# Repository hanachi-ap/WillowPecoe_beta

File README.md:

# WillowPecoe_beta

全国のWillowファンの皆様こんにちは。そしてβテストへようこそ。

## ビルドガイド(玄人向け)

MCUにProMicroを採用し、CherryMXスイッチ、PCB 3層サンドイッチと、ごくオーソドックスなスタイルを
採用しているので難しいところはないと思います。

基板がリバーシブルになっているので、パーツの取付面だけ注意ください。

## パーツリスト

- Pro Micro x1
- タクトスイッチ(2本足) x1
- MX用スイッチソケット x49
- ダイオード (TH or SMD) x50 
- フルカラーシリアルLED WS2812B x15 (opt)
- ロータリーエンコーダ x1  (opt)
  プッシュスイッチ対応。

  遊舎工房で販売している アメリカBourns社製 PEC12R-4222F-S0024 で動作を確認しています。
  その他秋月電子で販売しているロータリーエンコーダ（商品番号P-06357)もプシュスイッチ機能はありませんが動作確認済みです。

- 六角スペーサー(M2 7mm)  x13
- 六角スペーサー(M2 3.5mm) x6
- ネジ (M2 3mm) x38
- 2Uスタビライザ x1
- Cherry MX互換スイッチ x49
- キーキャップ (お好み)
  
## パーツの取付け
### 基板の表裏を決定
まず ロータリーエンコーダの位置を右か左か決めます。
 - 左側に置く場合、PCBのSide Aが表面になります。
 - 右側に置く場合、PCBのSide Bが表面になります。

### パーツのはんだ付け

#### ダイオード
- ダイオードは すべて裏面に取り付けます。 
  - SMD、TH どちらでも使えます。
  - 実際のところダイオードは表面につけても有効です。(見栄えの問題)
### スイッチソケット
- スイッチソケットはすべて裏面に取り付けます。

### RGB LED
- 表面側のパッドをジャンプさせます (Jump front sideと書いてあるところ)

- 表面に 3個、 裏面に12個取り付けます。
  - Side Aが表面の場合、 シルクのLED1からLED13に取り付けます。
  - Side Bが表面の場合、 シルクのLED16からLED30に取り付けます。

### ロータリーエンコーダ
- 表面からさして裏面をはんだ付けします。

### Pro Micro
 - ProMicroはコンスルーを使って表面に取り付けます。
 - ProMicroの実装面が内向きになるようにしてください。

### タクトスイッチ
  - 表面に取り付けます

## 組み立て

- トッププレートとPCBを3.5mmスペーサを使って取り付けます。
- スイッチを差し込みます。
- PCBと化粧板を7mmスペーサを使って取り付けます。
- トッププレートとボトムプレートを7mmスペーサを使って取り付けます。

## ファームウェア

- コンパイルしてください。ロリコンの位置によってキーマップが異なります。
  - Side A用: default
  - Side B用: side_b
  
## 既知の問題点

- アンダーグローの光がうまく廻りません。
  - アクリルプレートオプションを考慮します
  - 次の版では、簡単に表面の3つだけ優先的に光らせられるよう配線を見直します。
  - とりあえず表側の3個だけを光らすには 最初の5個だけを取り付けるか、ジャンパを這わせればOK。  

- PCBの表面に細かい油染みのような塗装ムラ?があります。
  - 製造委託先の品質に依存する問題かと思います。実質影響はありません。
  - 次の発注は別なところを考えてみます(量産のときはJLCPCBの価格は魅力なんだけど)
  
- ネジとスイッチが干渉する恐れがあるかも?
  - 作者手元のスイッチでは爪一枚入るくらいの余裕がありますが次の基板ではもう少し余裕持たせるようにします

- ファームウェアは開発途中です

- トッププレートのLEDを透過するスリットにはアクリルを埋め込む計画がありますが未実装です。
 
- 細かいキーレイアウトが作者の理想から少しだけ外れています。
  全体ををもう少し折り曲げたほうが好みなので修正が入るかもしれません

## 権利等
まだLICENSEを明記してませんが下記で公開する予定です。

- ファームウェア: GPL V2
- KiCAD設計データ: GPL V2
- KiCADフットプリント: MIT (thx foostan)
- 配列意匠: CC BY-SA 4.0 

以上です

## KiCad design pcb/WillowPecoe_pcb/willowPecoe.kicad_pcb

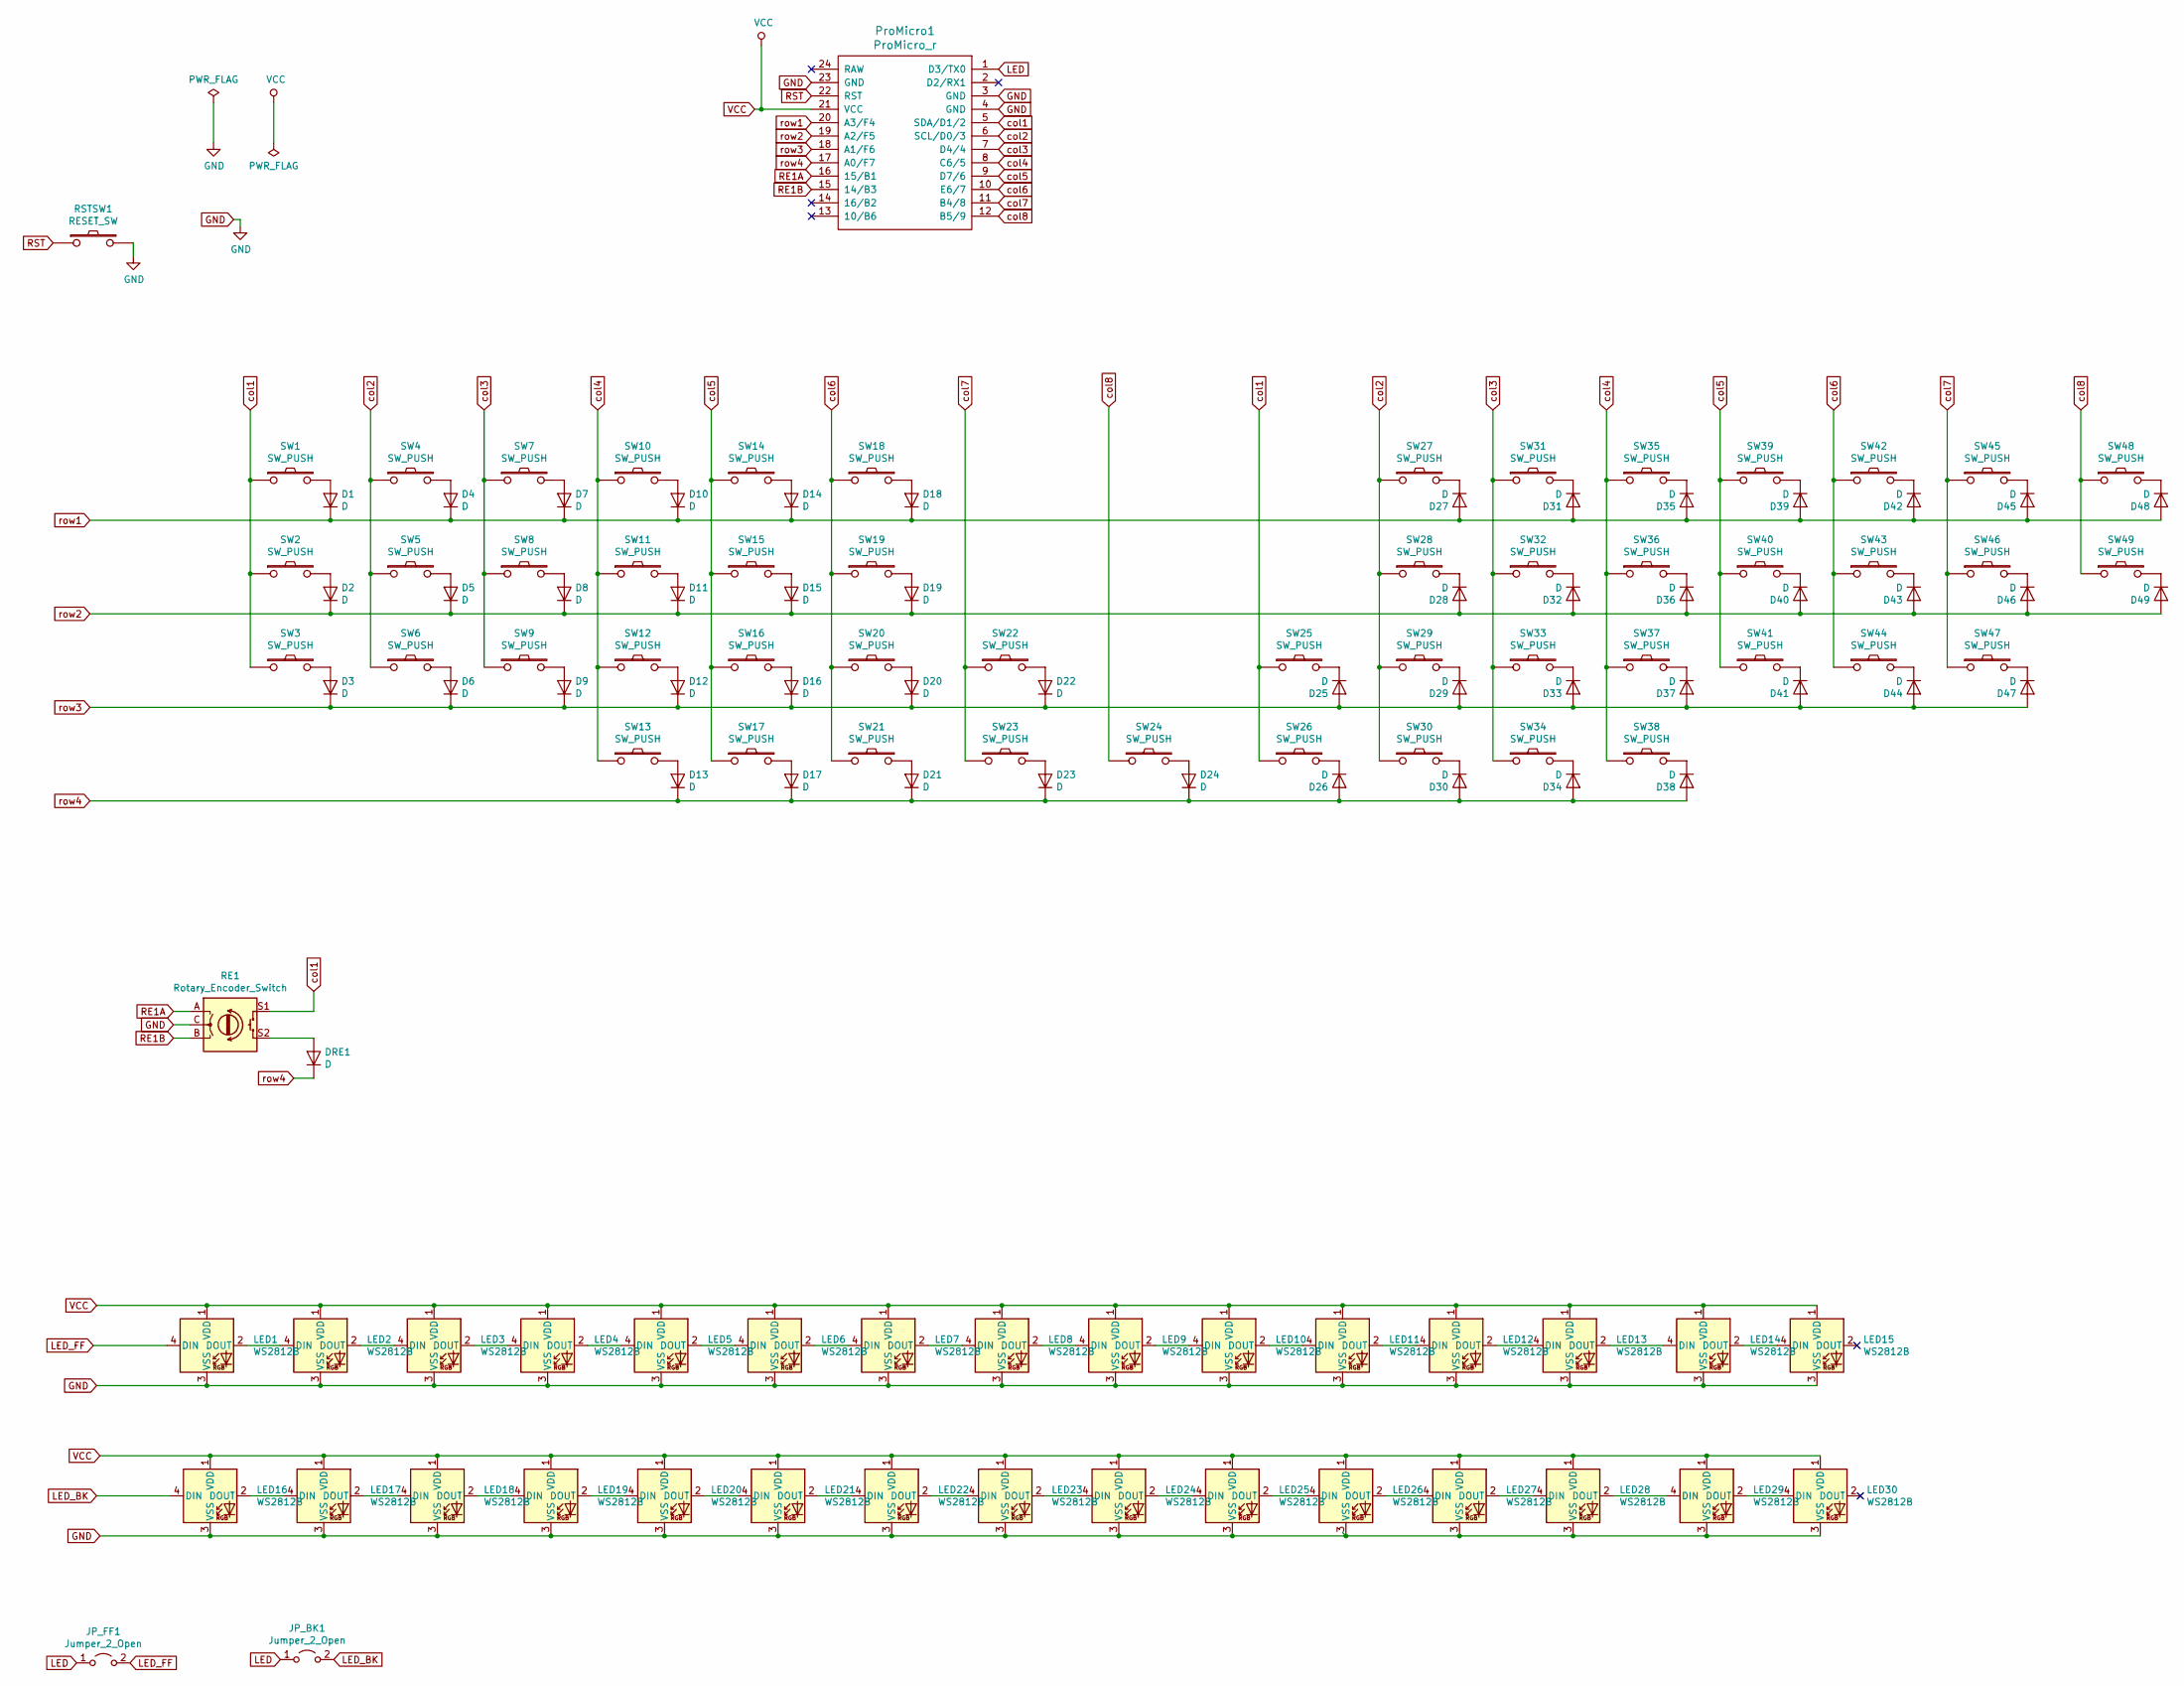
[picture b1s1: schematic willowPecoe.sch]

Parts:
D1, D2, D3, D4, D5, D6, D7, D8, D9, D10, D11, D12, D13, D14, D15, D16, D17, D18, D19, D20, D21, D22, D23, D24, D25, D26, D27, D28, D29, D30, D31, D32, D33, D34, D35, D36, D37, D38, D39, D40, D41, D42, D43, D44, D45, D46, D47, D48, D49: D; D3_TH_SMD
DRE1: D; D3_TH_SMD
JP_BK1: Jumper_2_Open; SolderJumper-2_P1.3mm_Open_RoundedPad1.0x1.5mm
JP_FF1: Jumper_2_Open; SolderJumper-2_P1.3mm_Open_RoundedPad1.0x1.5mm
LED1, LED2, LED3, LED4, LED5, LED6, LED7, LED8, LED9, LED10, LED11, LED12, LED13, LED14, LED15, LED16, LED17, LED18, LED19, LED20, LED21, LED22, LED23, LED24, LED25, LED26, LED27, LED28, LED29, LED30: WS2812B; LED_WS2812B_PLCC4_5.0x5.0mm_P3.2mm
ProMicro1: ProMicro_r; ProMicro_v2
RE1: Rotary_Encoder_Switch; RotaryEncoder_Alps_EC11E-Switch_Vertical_H20mm_rev2
RSTSW1: RESET_SW; ResetSW
SW1, SW2, SW3, SW4, SW5, SW6, SW7, SW8, SW9, SW10, SW11, SW12, SW13, SW14, SW15, SW16, SW17, SW18, SW19, SW20, SW21, SW22, SW23, SW24, SW25, SW26, SW27, SW28, SW29, SW30, SW31, SW32, SW33, SW34, SW35, SW36, SW37, SW38, SW39, SW40, SW41, SW42, SW43, SW44, SW45, SW46, SW47, SW48, SW49: SW_PUSH; CherryMX_MidHeight_Hotswap

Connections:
GND: LED1.3 (VSS), LED2.3 (VSS), LED3.3 (VSS), LED4.3 (VSS), LED5.3 (VSS), LED6.3 (VSS), LED7.3 (VSS), LED8.3 (VSS), LED9.3 (VSS), LED10.3 (VSS), LED11.3 (VSS), LED12.3 (VSS), LED13.3 (VSS), LED14.3 (VSS), LED15.3 (VSS), LED16.3 (VSS), LED17.3 (VSS), LED18.3 (VSS), LED19.3 (VSS), LED20.3 (VSS), LED21.3 (VSS), LED22.3 (VSS), LED23.3 (VSS), LED24.3 (VSS), LED25.3 (VSS), LED26.3 (VSS), LED27.3 (VSS), LED28.3 (VSS), LED29.3 (VSS), LED30.3 (VSS), ProMicro1.3 (GND), ProMicro1.4 (GND), ProMicro1.23 (GND), RE1.C, RSTSW1.2
LED: JP_BK1.1 (A), JP_FF1.1 (A), ProMicro1.1 (D3/TX0); also elsewhere on the board
LED_BK: JP_BK1.2 (B), LED16.4 (DIN); also elsewhere on the board
LED_FF: JP_FF1.2 (B), LED1.4 (DIN); also elsewhere on the board
unnamed: D1.2 (A), SW1.2
unnamed: D2.2 (A), SW2.2
unnamed: D3.2 (A), SW3.2
unnamed: D4.2 (A), SW4.2
unnamed: D5.2 (A), SW5.2
unnamed: D6.2 (A), SW6.2
unnamed: D7.2 (A), SW7.2
unnamed: D8.2 (A), SW8.2
unnamed: D9.2 (A), SW9.2
unnamed: D10.2 (A), SW10.2
unnamed: D11.2 (A), SW11.2
unnamed: D12.2 (A), SW12.2
unnamed: D13.2 (A), SW13.2
unnamed: D14.2 (A), SW14.2
unnamed: D15.2 (A), SW15.2
unnamed: D16.2 (A), SW16.2
unnamed: D17.2 (A), SW17.2
unnamed: D18.2 (A), SW18.2
unnamed: D19.2 (A), SW19.2
unnamed: D20.2 (A), SW20.2
unnamed: D21.2 (A), SW21.2
unnamed: D22.2 (A), SW22.2
unnamed: D23.2 (A), SW23.2
unnamed: D24.2 (A), SW24.2
unnamed: D25.1 (K), SW25.2
unnamed: D26.1 (K), SW26.2
unnamed: D27.1 (K), SW27.2
unnamed: D28.1 (K), SW28.2
unnamed: D29.1 (K), SW29.2
unnamed: D30.1 (K), SW30.2
unnamed: D31.1 (K), SW31.2
unnamed: D32.1 (K), SW32.2
unnamed: D33.1 (K), SW33.2
unnamed: D34.1 (K), SW34.2
unnamed: D35.1 (K), SW35.2
unnamed: D36.1 (K), SW36.2
unnamed: D37.1 (K), SW37.2
unnamed: D38.1 (K), SW38.2
unnamed: D39.1 (K), SW39.2
unnamed: D40.1 (K), SW40.2
unnamed: D41.1 (K), SW41.2
unnamed: D42.1 (K), SW42.2
unnamed: D43.1 (K), SW43.2
unnamed: D44.1 (K), SW44.2
unnamed: D45.1 (K), SW45.2
unnamed: D46.1 (K), SW46.2
unnamed: D47.1 (K), SW47.2
unnamed: D48.1 (K), SW48.2
unnamed: D49.1 (K), SW49.2
unnamed: DRE1.2 (A), RE1.S2
unnamed: LED1.2 (DOUT), LED2.4 (DIN)
unnamed: LED2.2 (DOUT), LED3.4 (DIN)
unnamed: LED3.2 (DOUT), LED4.4 (DIN)
unnamed: LED4.2 (DOUT), LED5.4 (DIN)
unnamed: LED5.2 (DOUT), LED6.4 (DIN)
unnamed: LED6.2 (DOUT), LED7.4 (DIN)
unnamed: LED7.2 (DOUT), LED8.4 (DIN)
unnamed: LED8.2 (DOUT), LED9.4 (DIN)
unnamed: LED10.2 (DOUT), LED11.4 (DIN)
unnamed: LED9.2 (DOUT), LED10.4 (DIN)
unnamed: LED11.2 (DOUT), LED12.4 (DIN)
unnamed: LED12.2 (DOUT), LED13.4 (DIN)
unnamed: LED13.2 (DOUT), LED14.4 (DIN)
unnamed: LED14.2 (DOUT), LED15.4 (DIN)
unnamed: LED16.2 (DOUT), LED17.4 (DIN)
unnamed: LED17.2 (DOUT), LED18.4 (DIN)
unnamed: LED18.2 (DOUT), LED19.4 (DIN)
unnamed: LED19.2 (DOUT), LED20.4 (DIN)
unnamed: LED20.2 (DOUT), LED21.4 (DIN)
unnamed: LED21.2 (DOUT), LED22.4 (DIN)
unnamed: LED22.2 (DOUT), LED23.4 (DIN)
unnamed: LED23.2 (DOUT), LED24.4 (DIN)
unnamed: LED24.2 (DOUT), LED25.4 (DIN)
unnamed: LED25.2 (DOUT), LED26.4 (DIN)
unnamed: LED26.2 (DOUT), LED27.4 (DIN)
unnamed: LED27.2 (DOUT), LED28.4 (DIN)
unnamed: LED28.2 (DOUT), LED29.4 (DIN)
unnamed: LED29.2 (DOUT), LED30.4 (DIN)
RE1A: ProMicro1.16 (15/B1), RE1.A
RE1B: ProMicro1.15 (14/B3), RE1.B
RST: ProMicro1.22 (RST), RSTSW1.1
VCC: LED1.1 (VDD), LED2.1 (VDD), LED3.1 (VDD), LED4.1 (VDD), LED5.1 (VDD), LED6.1 (VDD), LED7.1 (VDD), LED8.1 (VDD), LED9.1 (VDD), LED10.1 (VDD), LED11.1 (VDD), LED12.1 (VDD), LED13.1 (VDD), LED14.1 (VDD), LED15.1 (VDD), LED16.1 (VDD), LED17.1 (VDD), LED18.1 (VDD), LED19.1 (VDD), LED20.1 (VDD), LED21.1 (VDD), LED22.1 (VDD), LED23.1 (VDD), LED24.1 (VDD), LED25.1 (VDD), LED26.1 (VDD), LED27.1 (VDD), LED28.1 (VDD), LED29.1 (VDD), LED30.1 (VDD), ProMicro1.21 (VCC)
col1: ProMicro1.5 (SDA/D1/2), RE1.S1, SW1.1, SW2.1, SW3.1, SW25.1, SW26.1
col2: ProMicro1.6 (SCL/D0/3), SW4.1, SW5.1, SW6.1, SW27.1, SW28.1, SW29.1, SW30.1
col3: ProMicro1.7 (D4/4), SW7.1, SW8.1, SW9.1, SW31.1, SW32.1, SW33.1, SW34.1
col4: ProMicro1.8 (C6/5), SW10.1, SW11.1, SW12.1, SW13.1, SW35.1, SW36.1, SW37.1, SW38.1
col5: ProMicro1.9 (D7/6), SW14.1, SW15.1, SW16.1, SW17.1, SW39.1, SW40.1, SW41.1
col6: ProMicro1.10 (E6/7), SW18.1, SW19.1, SW20.1, SW21.1, SW42.1, SW43.1, SW44.1
col7: ProMicro1.11 (B4/8), SW22.1, SW23.1, SW45.1, SW46.1, SW47.1
col8: ProMicro1.12 (B5/9), SW24.1, SW48.1, SW49.1
row1: D1.1 (K), D4.1 (K), D7.1 (K), D10.1 (K), D14.1 (K), D18.1 (K), D27.2 (A), D31.2 (A), D35.2 (A), D39.2 (A), D42.2 (A), D45.2 (A), D48.2 (A), ProMicro1.20 (A3/F4)
row2: D2.1 (K), D5.1 (K), D8.1 (K), D11.1 (K), D15.1 (K), D19.1 (K), D28.2 (A), D32.2 (A), D36.2 (A), D40.2 (A), D43.2 (A), D46.2 (A), D49.2 (A), ProMicro1.19 (A2/F5)
row3: D3.1 (K), D6.1 (K), D9.1 (K), D12.1 (K), D16.1 (K), D20.1 (K), D22.1 (K), D25.2 (A), D29.2 (A), D33.2 (A), D37.2 (A), D41.2 (A), D44.2 (A), D47.2 (A), ProMicro1.18 (A1/F6)
row4: D13.1 (K), D17.1 (K), D21.1 (K), D23.1 (K), D24.1 (K), D26.2 (A), D30.2 (A), D34.2 (A), D38.2 (A), DRE1.1 (K), ProMicro1.17 (A0/F7)

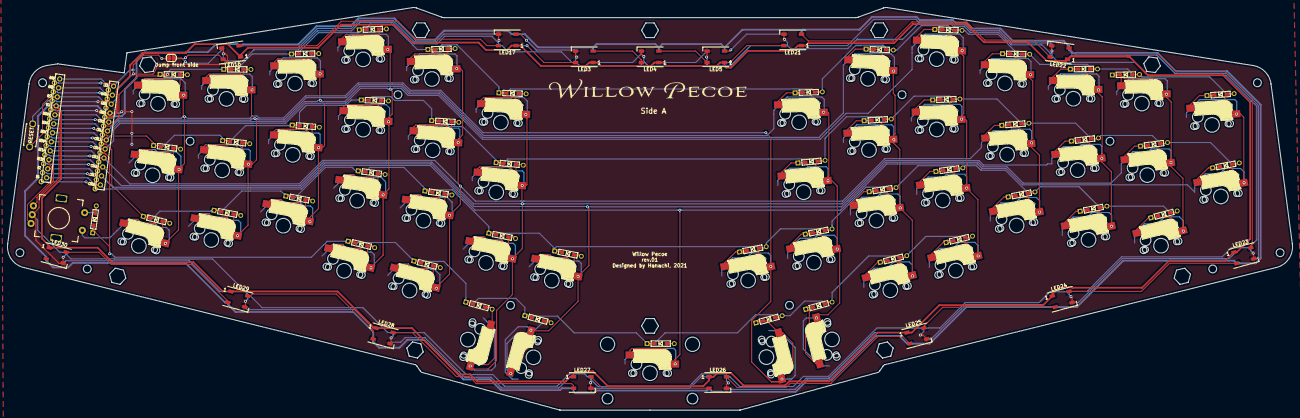
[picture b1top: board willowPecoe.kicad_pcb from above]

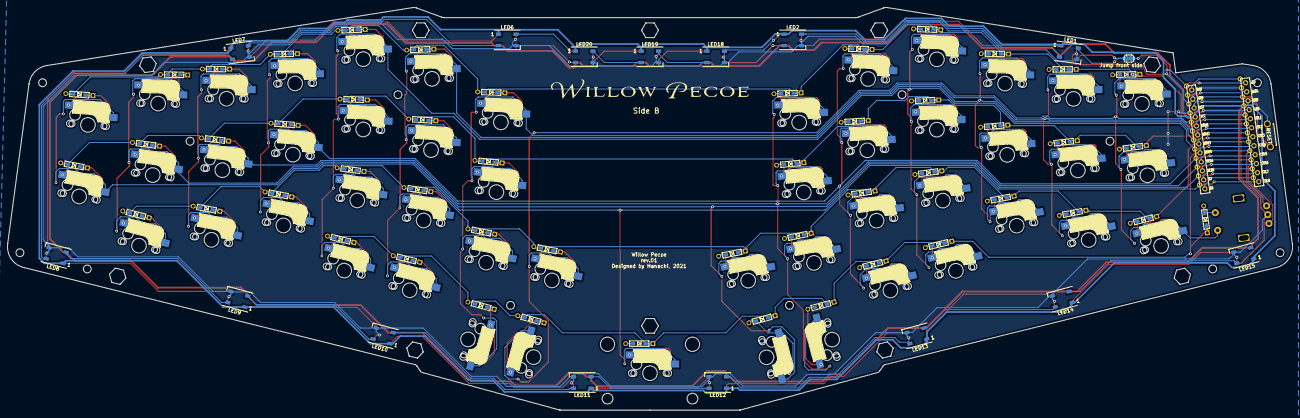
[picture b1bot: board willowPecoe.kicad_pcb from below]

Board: 2 copper layers, 360.1 x 112.8 mm, 134 parts (16 on the bottom side), 98 nets.

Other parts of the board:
Jump front side: Jumper_2_Open; SolderJumper-2_P1.3mm_Open_RoundedPad1.0x1.5mm
Jump front side#2: Jumper_2_Open; SolderJumper-2_P1.3mm_Open_RoundedPad1.0x1.5mm

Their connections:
LED: Jump front side.1, Jump front side#2.1; also elsewhere on the board
LED_BK: Jump front side.2; also elsewhere on the board
LED_FF: Jump front side#2.2; also elsewhere on the board

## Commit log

2021-04-15 add README.md
2021-04-16 add qmk_firmware, pcb, via
2021-04-16 add pcb/kicad_lib
2021-04-16 fix kicad library path
2021-04-17 modify: README.md
2021-04-18 add "test" keymap. enable LTO for size
2021-04-18 add "test" keymap. enable LTO for size (#2)
2021-06-12 Set theme jekyll-theme-cayman
